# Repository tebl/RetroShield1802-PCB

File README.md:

# RetroShield 1802 PCB

Based on software and designs by Erturk Kocalar, this Arduino Mega 2560 shield adds a supplemental 1802 processor allowing you to run all the latest software developed for the 1802! By latest we ofcourse mean retro since it is a processor developed all the way back in 1976, but all the fun is still there so grab it while you can. More information about the shield available over at the [gitlab.com/8bitforce/retroshield1802/](https://gitlab.com/8bitforce/retroshield1802/tree/master).

Initial version of PCB layout done by Tor-Eirik Bakke Lunde, usually pushing files to [github.com/tebl](https://github.com/tebl). Arduino layouts and footprints from [github.com/Alarm-Siren/arduino-kicad-library](https://github.com/Alarm-Siren/arduino-kicad-library).

# Schematic
The supplied KiCad files should be sufficient as both a schematic and as a  starting point for ordering PCBs (basically you could just zip the contents of the export folder and upload that on a fabrication site), the schematic is also available in [PDF-format](https://gitlab.com/8bitforce/retroshield1802/raw/master/docs/k1802_sch_revB.pdf?inline=false) and this is what you'll need to print and work your way through this things don't work as expected after assembly. Schematic as adapted for KiCad and basis for PCB layout, also available in [PDF-format](https://github.com/tebl/RetroShield1802-PCB/raw/master/export/Retroshield1802-PCB.pdf).

# BOM
Most parts should be easy to get a hold of from your favourite local electronic component shop though you might have to consider other sources for the older parts such as the CPU and memory. Personally I bought most components with free shipping from China via AliExpress - prices will vary, but I found everything in larger quantities than needed for the cost of a few cups of fancy coffee! You don't need the newest and fastest components, after all it's going into a 70s-era computer so don't go overboard unless you want to.

Some vendors will have the same ICs in different form factors, the ones you want will often be specified as being in the form of a DIP/PDIP package. Usually you'll want sockets for each of the ICs as well, a bag of assorted sockets should be easily available without setting you back more than a couple bucks. With the sockets in place, you don't need to dread having to remove an IC later, this leads to easier fault finding and you can even "borrow" them for other projects later! For the pin headers, you probably won't find the exact pin count so just buy the longer versions and snip off the parts you don't need.

Values in parenthesis is the component amounts that could be considered optional or relating to alternative construction options.

| Reference    | Item                                  | Count |
| ------------ | ------------------------------------- | ----- |
| PCB          | Fabricate using Gerber files ([order](https://www.pcbway.com/project/shareproject/RetroShield_1802.html?inviteid=88707))  |     1 |
| C1-C2        | 100nF ceramic capacitor               |     2 |
| C3           | 22pF ceramic capacitor                |     2 |
| D1-D2        | 5mm LED (assorted colours)            |     2 |
| IC1          | 0.96" I2C OLED (optional)             |   (1) |
| R1           | 33 ohm resistor                       |     1 |
| R2-R6        | 680 ohm resistor                      |     5 |
| R7           | Piece of wire (if not installing R8)  |    (1)|
| R8           | Piece of wire                         |     1 |
| U1           | CDP1802 CPU DIP-40                    |     1 |
|              | Male 40-pin header (break to size)    |     2 |
|              | Male 2x40-pin header (break to size)  |     1 |

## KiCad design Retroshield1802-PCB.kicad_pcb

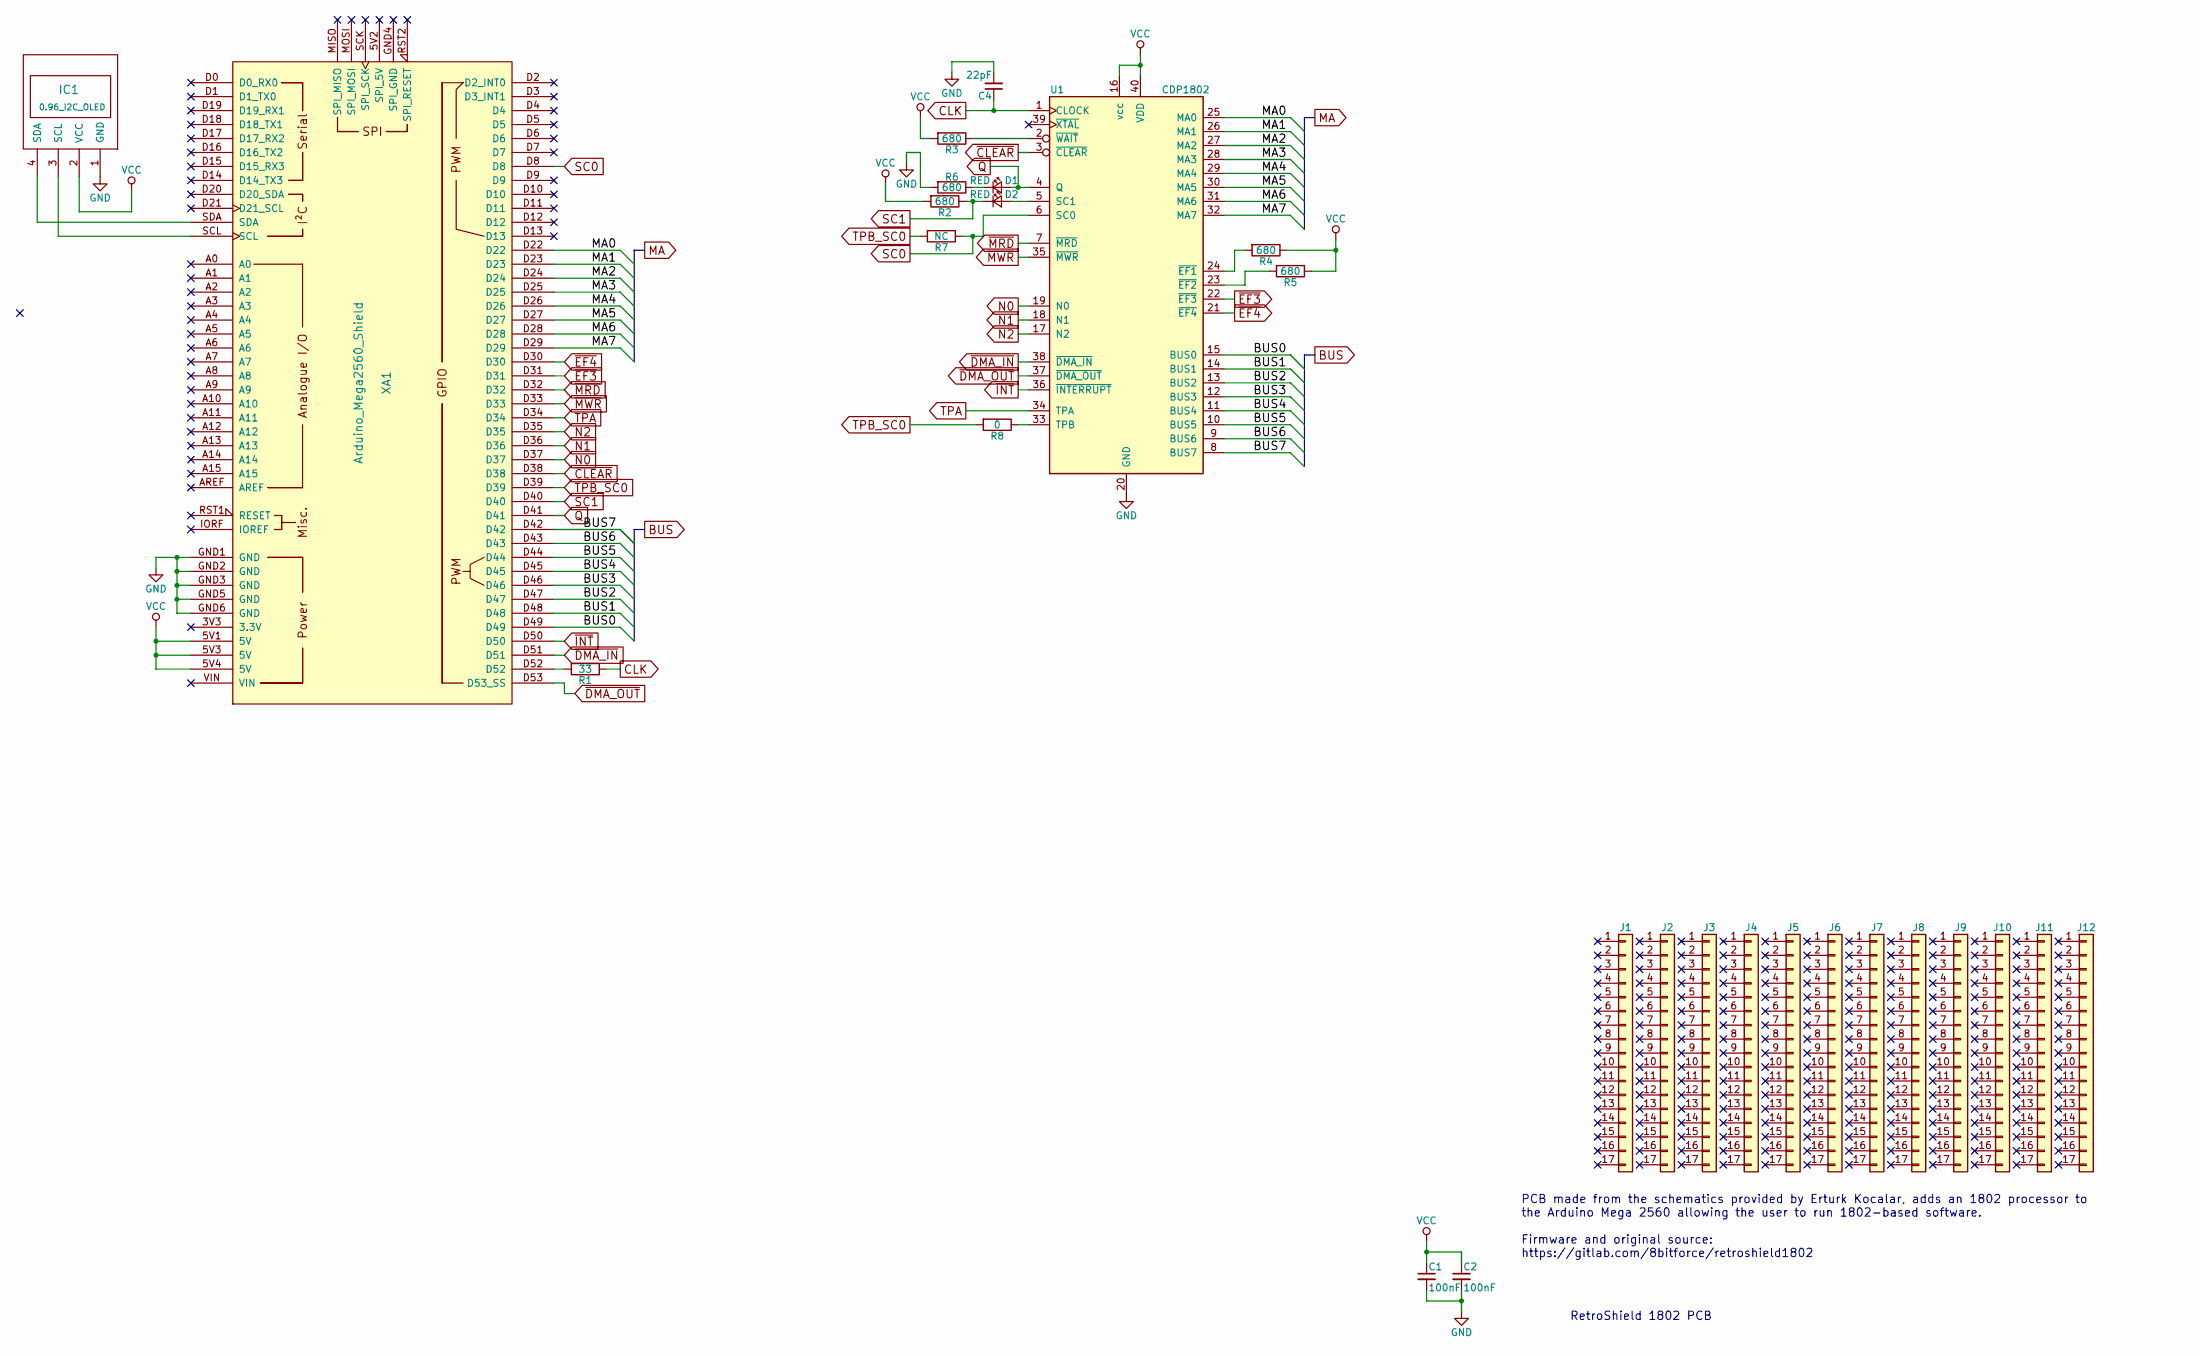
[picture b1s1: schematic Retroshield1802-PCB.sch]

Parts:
C1, C2: 100nF; C_Disc_D4.7mm_W2.5mm_P5.00mm
C4: 22pF; C_Disc_D4.7mm_W2.5mm_P5.00mm
D1, D2: RED; LED_D5.0mm
IC1: 0.96_I2C_OLED
J1, J2, J3, J4, J5, J6, J7, J8, J9, J10, J11, J12: Conn_01x17; 17
R1: 33; R_Axial_DIN0207_L6.3mm_D2.5mm_P10.16mm_Horizontal
R2, R3, R4, R5, R6: 680; R_Axial_DIN0207_L6.3mm_D2.5mm_P10.16mm_Horizontal
R7: NC; R_Axial_DIN0207_L6.3mm_D2.5mm_P10.16mm_Horizontal
R8: 0; R_Axial_DIN0207_L6.3mm_D2.5mm_P10.16mm_Horizontal
U1: CDP1802; DIP-40_W15.24mm_Socket
XA1: Arduino_Mega2560_Shield

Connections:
/BUS0: U1.15 (BUS0), XA1.D49
/BUS1: U1.14 (BUS1), XA1.D48
/BUS2: U1.13 (BUS2), XA1.D47
/BUS3: U1.12 (BUS3), XA1.D46
/BUS4: U1.11 (BUS4), XA1.D45
/BUS5: U1.10 (BUS5), XA1.D44
/BUS6: U1.9 (BUS6), XA1.D43
/BUS7: U1.8 (BUS7), XA1.D42
/MA0: U1.25 (MA0), XA1.D22
/MA1: U1.26 (MA1), XA1.D23
/MA2: U1.27 (MA2), XA1.D24
/MA3: U1.28 (MA3), XA1.D25
/MA4: U1.29 (MA4), XA1.D26
/MA5: U1.30 (MA5), XA1.D27
/MA6: U1.31 (MA6), XA1.D28
/MA7: U1.32 (MA7), XA1.D29
CLK: C4.1, R1.1, U1.1 (CLOCK)
GND: C1.2, C2.2, C4.2, IC1.1 (GND), R6.2, U1.20 (GND), XA1.GND1 (GND), XA1.GND2 (GND), XA1.GND3 (GND), XA1.GND5 (GND), XA1.GND6 (GND)
N0: U1.19 (N0), XA1.D37
N1: U1.18 (N1), XA1.D36
N2: U1.17 (N2), XA1.D35
unnamed: D1.1 (K), R6.1
unnamed: D2.2 (A), U1.5 (SC1)
unnamed: IC1.3 (SCL), XA1.SCL
unnamed: IC1.4 (SDA), XA1.SDA
unnamed: R1.2, XA1.D52
unnamed: R3.1, U1.2 (~WAIT~)
unnamed: R4.2, U1.24 (~EF1)
unnamed: R5.2, U1.23 (~EF2)
unnamed: R8.1, U1.33 (TPB)
Q: D1.2 (A), U1.4 (Q), XA1.D41
SC0: R7.1, U1.6 (SC0), XA1.D8
SC1: D2.1 (K), R2.1, XA1.D40
TPA: U1.34 (TPA), XA1.D34
TPB_SC0: R7.2, R8.2, XA1.D39
VCC: C1.1, C2.1, IC1.2 (VCC), R2.2, R3.2, R4.1, R5.1, U1.16 (vcc), U1.40 (VDD), XA1.5V1 (5V), XA1.5V3 (5V), XA1.5V4 (5V)
~CLEAR: U1.3 (~CLEAR), XA1.D38
~DMA_IN: U1.38 (~DMA_IN), XA1.D51
~DMA_OUT: U1.37 (~DMA_OUT), XA1.D53 (D53_SS)
~EF3: U1.22 (~EF3), XA1.D31
~EF4: U1.21 (~EF4), XA1.D30
~INT: U1.36 (~INTERRUPT), XA1.D50
~MRD: U1.7 (~MRD), XA1.D32
~MWR: U1.35 (~MWR), XA1.D33

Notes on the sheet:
RetroShield 1802 PCB
PCB made from the schematics provided by Erturk Kocalar, adds an 1802 processor to the Arduino Mega 2560 allowing the user to run 1802-based software. Firmware and original source: https://gitlab.com/8bitforce/retroshield1802

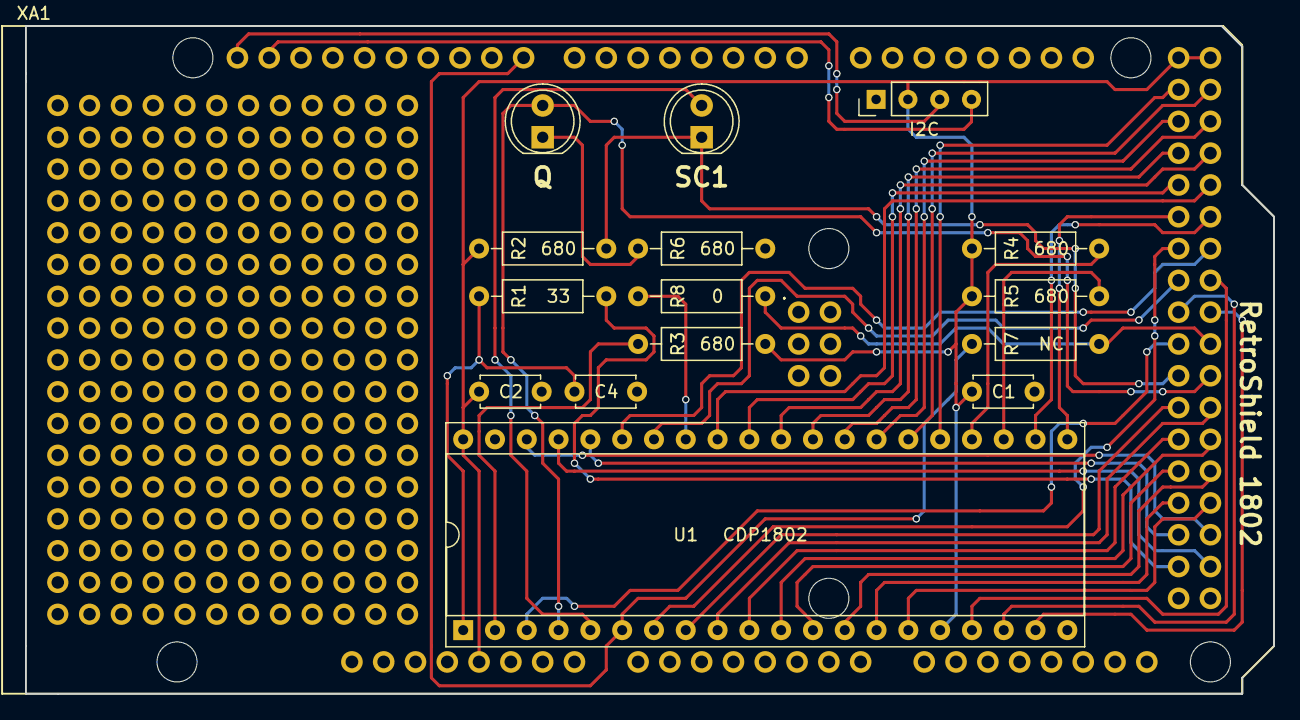
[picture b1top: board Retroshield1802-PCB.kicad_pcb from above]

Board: 2 copper layers, 99.7 x 53.3 mm, 28 parts (0 on the bottom side), 44 nets.

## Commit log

2019-08-20 Initial PCB
2019-08-20 Added header for 0.96" I2C displau
2019-08-20 Gerber export
2019-08-20 Added README
2019-08-20 Added name
2019-08-20 Added Arduino symbol/footprint notice
